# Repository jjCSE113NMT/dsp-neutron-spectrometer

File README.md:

# dsp-neutron-spectrometer

A place to keep all our material related to our senior design project.

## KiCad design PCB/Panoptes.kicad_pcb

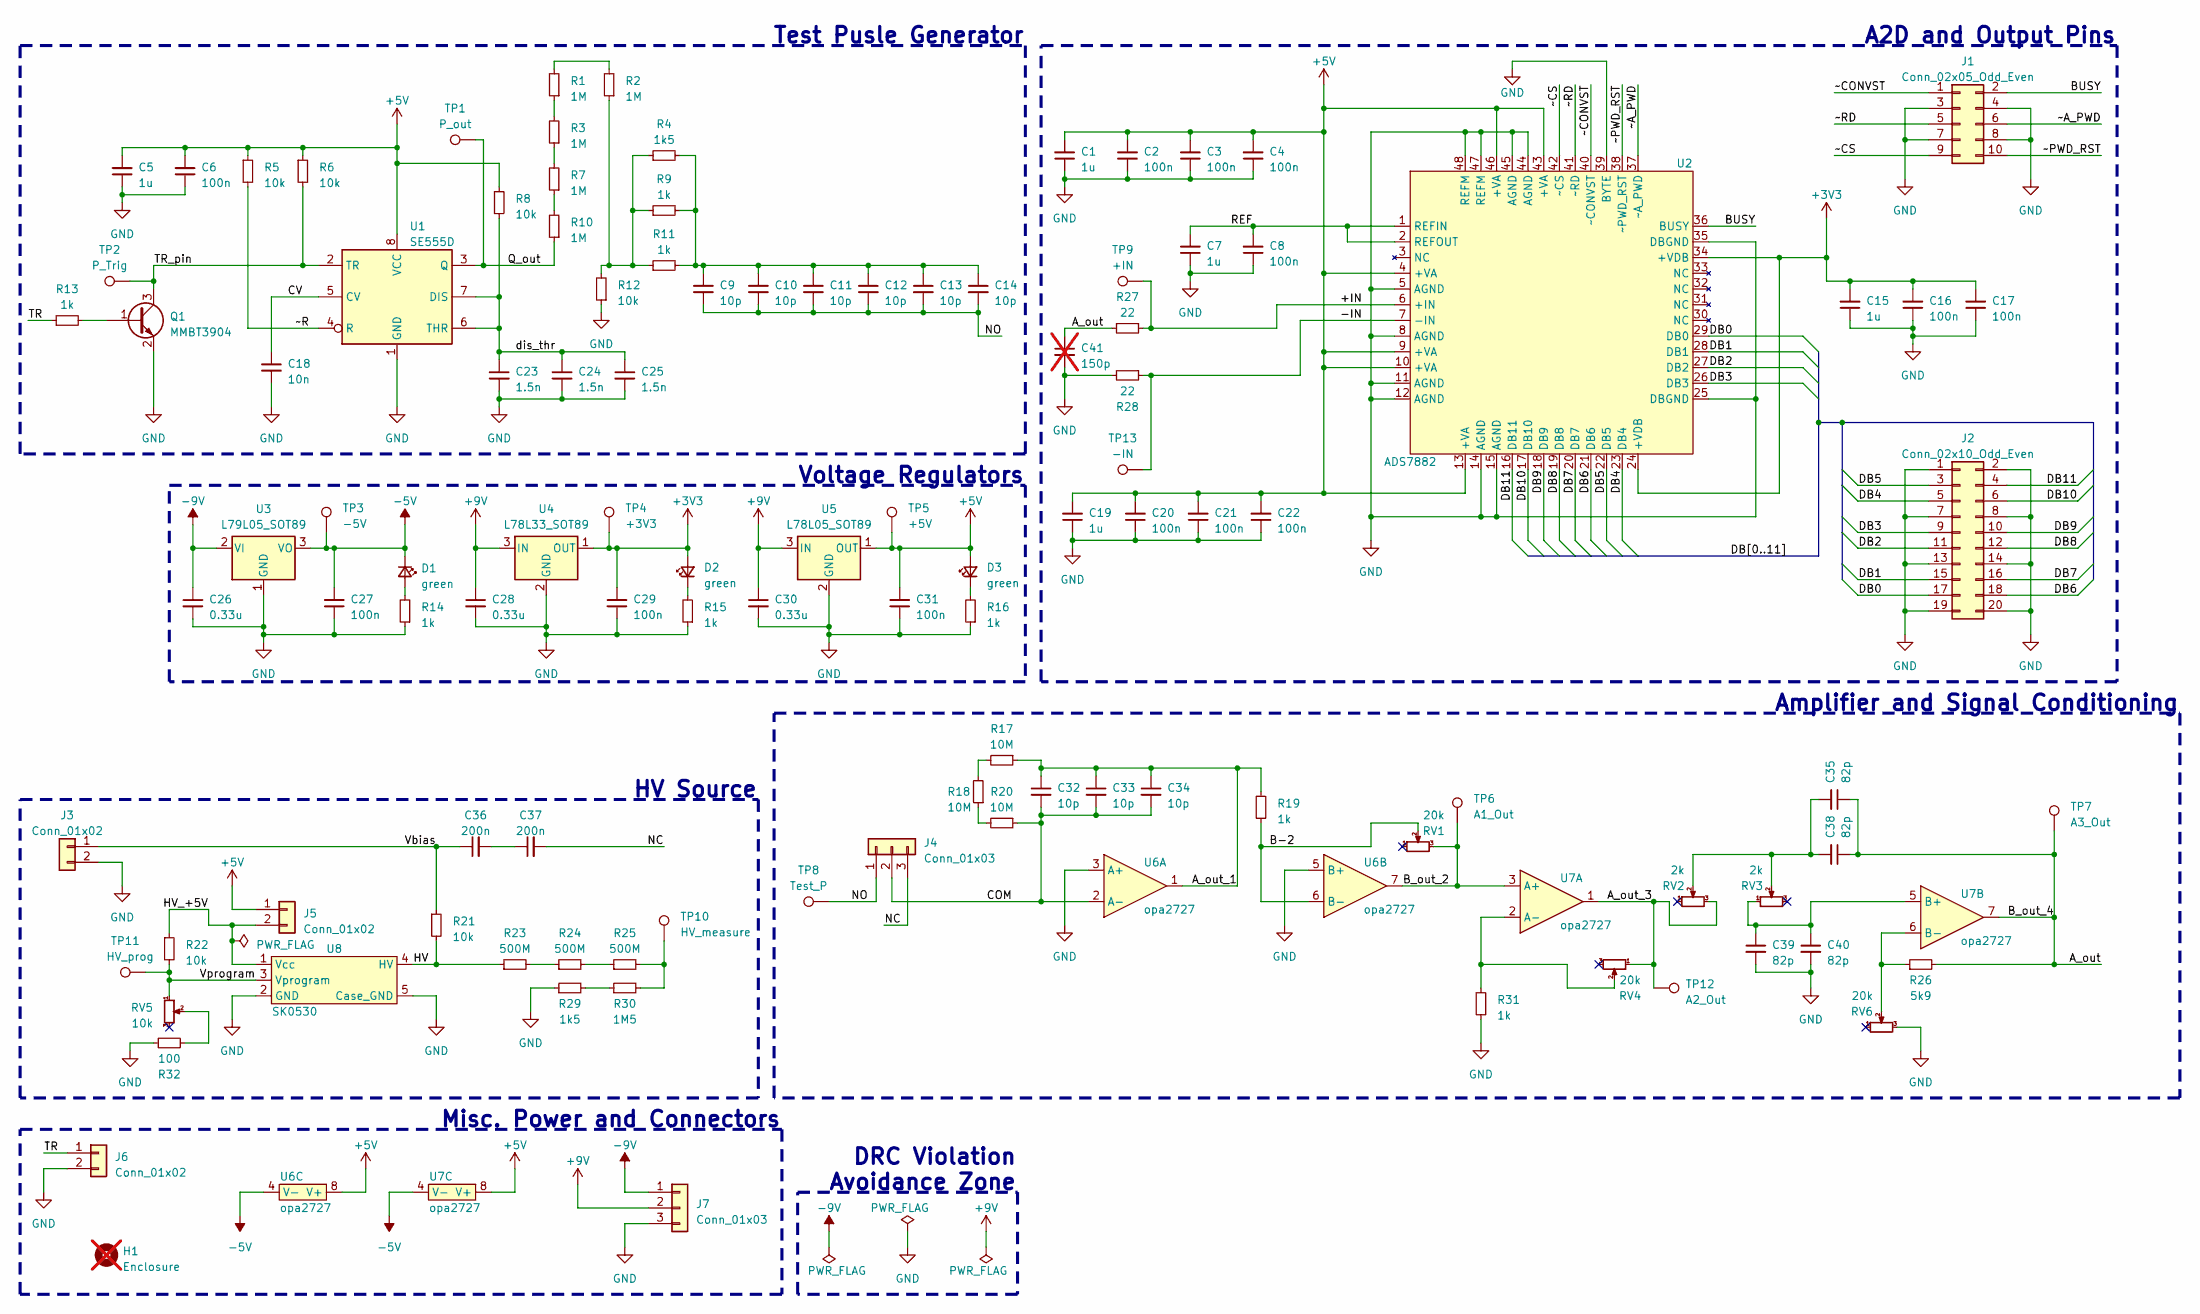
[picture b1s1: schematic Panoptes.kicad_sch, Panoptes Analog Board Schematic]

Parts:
C1, C5, C7, C15, C19: 1u; C_1206_3216Metric; MPN CL31B105KAHNNNE
C2, C3, C4, C6, C8, C16, C17, C20, C21, C22, C27, C29, C31: 100n; C_1206_3216Metric; MPN CL31B104KBCNNNC
C9, C10, C11, C12, C13, C14, C32, C33, C34: 10p; C_1206_3216Metric; MPN C1206C100F1HACAUTO
C18: 10n; C_1206_3216Metric; MPN C1206C103JARAC7800
C23, C24, C25: 1.5n; C_1206_3216Metric; MPN CC1206FRNPO9BN152
C26, C28, C30: 0.33u; C_1206_3216Metric; MPN CL31B334KBFNNNE
C35, C38, C39, C40: 82p; C_1206_3216Metric; MPN CC1206JRNPO9BN820
C36, C37: 200n; C_Disc_D10.5mm_W5.0mm_P7.50mm; MPN CK45-B3FD221KYGNA
C41: 150p; C_0603_1608Metric; not fitted
D1, D2, D3: green; LED_0805_2012Metric; MPN 150080VS75000
H1: Enclosure; n/a; MPN 1455N1201RD; not fitted
J1: Conn_02x05_Odd_Even; PinSocket_2x05_P2.54mm_Horizontal; MPN SFH11-PBPC-D05-RA-BK
J2: Conn_02x10_Odd_Even; PinSocket_2x10_P2.54mm_Horizontal; MPN SFH11-PBPC-D10-RA-BK
J3: Conn_01x02; tube pigtail; MPN n/a
J4: Conn_01x03; PinHeader_1x03_P2.54mm_Vertical; MPN n/a
J5: Conn_01x02; PinHeader_1x02_P2.54mm_Vertical; MPN n/a
J6: Conn_01x02; PinSocket_1x02_P2.54mm_Horizontal; MPN PPTC021LGBN-RC
J7: Conn_01x03; STX-3500-3NTR; MPN STX-3500-3NTR
Q1: MMBT3904; SOT-23-3; MPN MMBT3904-TP
R1, R2, R3, R7, R10: 1M; R_1206_3216Metric; MPN RMCF1206FT1M00
R4, R29: 1k5; R_1206_3216Metric; MPN RMCF1206FT1K50
R5, R6, R8, R12, R21, R22: 10k; R_1206_3216Metric; MPN RMCF1206FT10K0
R9, R11, R13, R14, R15, R16, R19, R31: 1k; R_1206_3216Metric; MPN RMCF1206FT1K00
R17, R18, R20: 10M; R_1206_3216Metric; MPN RMCF1206FT10M0
R23, R24, R25: 500M; R_Axial_DIN0207_L6.3mm_D2.5mm_P7.62mm_Horizontal; MPN HVA05FA500M
R26: 5k9; R_1206_3216Metric; MPN CRCW12065K90FKEA
R27, R28: 22; R_1206_3216Metric; MPN RMCF1206FT22R0
R30: 1M5; R_1206_3216Metric; MPN RC1206FR-071M5L
R32: 100; R_1206_3216Metric; MPN RMCF1206FG100R
RV1, RV4, RV6: 20k; Bourns 3361P; MPN 3361P-1-203GLF
RV2, RV3: 2k; Bourns 3361P; MPN 3361P-1-202GLF
RV5: 10k; Bourns 3361P; MPN 3361P-1-103GLF
TP1: P_out; PinHeader_1x01_P2.54mm_Vertical; MPN n/a
TP2: P_Trig; PinHeader_1x01_P2.54mm_Vertical; MPN n/a
TP3: -5V; PinHeader_1x01_P2.54mm_Vertical; MPN n/a
TP4: +3V3; PinHeader_1x01_P2.54mm_Vertical; MPN n/a
TP5: +5V; PinHeader_1x01_P2.54mm_Vertical; MPN n/a
TP6: A1_Out; PinHeader_1x01_P2.54mm_Vertical; MPN n/a
TP7: A3_Out; PinHeader_1x01_P2.54mm_Vertical; MPN n/a
TP8: Test_P; PinHeader_1x01_P2.54mm_Vertical; MPN n/a
TP9: +IN; PinHeader_1x01_P2.54mm_Vertical; MPN n/a
TP10: HV_measure; TestPoint_Pad_D1.0mm; MPN n/a
TP11: HV_prog; TestPoint_Pad_D1.0mm; MPN n/a
TP12: A2_Out; PinHeader_1x01_P2.54mm_Vertical; MPN n/a
TP13: -IN; PinHeader_1x01_P2.54mm_Vertical; MPN n/a
U1: SE555D; SOIC-8_3.9x4.9mm_P1.27mm; MPN SE555DR
U2: ADS7882; TQFP-48_7x7mm_P0.5mm; MPN ADS7882IPFBT
U3: L79L05_SOT89; SOT-89-3; MPN L79L05ACUTR
U4: L78L33_SOT89; SOT-89-3; MPN L78L33ACUTR
U5: L78L05_SOT89; SOT-89-3; MPN L78L05ACUTR
U6, U7: opa2727; DFN-8-1EP_3x3mm_P0.65mm_EP1.55x2.4mm; MPN OPA2727AIDRBT
U8: SK0530; MPN SK0530

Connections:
+3V3: C15.2, C16.2, C17.2, C29.2, D2.2 (A), TP4.1, U2.24 (+VDB), U2.34 (+VDB), U4.1 (OUT)
+5V: C1.2, C2.2, C3.2, C4.2, C5.2, C6.2, C19.2, C20.2, C21.2, C22.2, C31.2, D3.2 (A), J5.1, R5.1, R6.1, R8.1, TP5.1, U1.8 (VCC), U2.4 (+VA), U2.9 (+VA), U2.10 (+VA), U2.13 (+VA), U2.43 (+VA), U2.46 (+VA), U5.1 (OUT), U6.8 (V+), U7.8 (V+)
+9V: C28.1, C30.1, J7.2, U4.3 (IN), U5.3 (IN)
-5V: C27.2, D1.1 (K), TP3.1, U3.3 (VO), U6.4 (V-), U7.4 (V-)
-9V: C26.1, J7.1, U3.2 (VI)
/+IN: R27.1, TP9.1, U2.6 (+IN)
/-IN: R28.1, TP13.1, U2.7 (-IN)
/A_out: C35.1, C38.1, C41.1, R26.2, R27.2, TP7.1, U7.7
/A_out_1: C32.1, C33.1, C34.1, R17.1, R19.1, U6.1
/A_out_3: RV2.3, RV4.1, TP12.1, U7.1
/B-2: R19.2, RV1.2, U6.6 (B-)
/BUSY: J1.2, U2.36 (BUSY)
/B_out_2: RV1.3, TP6.1, U6.7, U7.3 (A+)
/COM: C32.2, C33.2, C34.2, J4.2, R20.1, U6.2 (A-)
/CV: C18.1, U1.5 (CV)
/DB0: J2.17, U2.29 (DB0)
/DB1: J2.15, U2.28 (DB1)
/DB2: J2.11, U2.27 (DB2)
/DB3: J2.9, U2.26 (DB3)
/DB4: J2.5, U2.23 (DB4)
/DB5: J2.3, U2.22 (DB5)
/DB6: J2.18, U2.21 (DB6)
/DB7: J2.16, U2.20 (DB7)
/DB8: J2.12, U2.19 (DB8)
/DB9: J2.10, U2.18 (DB9)
/DB10: J2.6, U2.17 (DB10)
/DB11: J2.4, U2.16 (DB11)
/HV: R21.2, R23.1, U8.4 (HV)
/HV_+5V: J5.2, R22.1, U8.1 (Vcc)
/NC: C37.2, J4.3
/NO: C9.2, C10.2, C11.2, C12.2, C13.2, C14.2, J4.1, TP8.1
/Q_out: R10.1, TP1.1, U1.3 (Q)
/REF: C7.2, C8.2, U2.1 (REFIN), U2.2 (REFOUT)
/TR: J6.1, R13.1
/TR_pin: Q1.3 (C), R6.2, TP2.1, U1.2 (TR)
/Vbias: C36.1, J3.1, R21.1
/Vprogram: R22.2, RV5.1, TP11.1, U8.3 (Vprogram)
/dis_thr: C23.1, C24.1, C25.1, R8.2, U1.6 (THR), U1.7 (DIS)
/~A_PWD: J1.6, U2.37 (~A_PWD)
/~CONVST: J1.1, U2.40 (~CONVST)
/~CS: J1.9, U2.42 (~CS)
/~PWD_RST: J1.10, U2.38 (~PWD_RST)
/~R: R5.2, U1.4 (R)
/~RD: J1.5, U2.41 (~RD)
GND: C1.1, C2.1, C3.1, C4.1, C5.1, C6.1, C7.1, C8.1, C15.1, C16.1, C17.1, C18.2, C19.1, C20.1, C21.1, C22.1, C23.2, C24.2, C25.2, C26.2, C27.1, C28.2, C29.1, C30.2, C31.1, C39.2, C40.2, C41.2, J1.3, J1.4, J1.7, J1.8, J2.1, J2.2, J2.7, J2.8, J2.13, J2.14, J2.19, J2.20, J3.2, J6.2, J7.3, Q1.2 (E), R12.1, R14.1, R15.1, R16.1, R28.2, R29.1, R31.1, R32.1, RV6.3, U1.1 (GND), U2.5 (AGND), U2.8 (AGND), U2.11 (AGND), U2.12 (AGND), U2.14 (AGND), U2.15 (AGND), U2.25 (DBGND), U2.35 (DBGND), U2.39 (BYTE), U2.44 (AGND), U2.45 (AGND), U2.47 (REFM), U2.48 (REFM), U3.1 (GND), U4.2 (GND), U5.2 (GND), U6.3 (A+), U6.5 (B+), U8.2 (GND), U8.5 (Case_GND)
unnamed: C9.1, C10.1, C11.1, C12.1, C13.1, C14.1, R4.2, R9.2, R11.2
unnamed: C35.2, C38.2, RV2.2, RV3.2
unnamed: C36.2, C37.1
unnamed: D1.2 (A), R14.2
unnamed: D2.1 (K), R15.2
unnamed: D3.1 (K), R16.2
unnamed: Q1.1 (B), R13.2
unnamed: R1.1, R3.2
unnamed: R1.2, R2.2
unnamed: R3.1, R7.2
unnamed: R7.1, R10.2
unnamed: R2.1, R4.1, R9.1, R11.1, R12.2
unnamed: R17.2, R18.2
unnamed: R18.1, R20.2
unnamed: R23.2, R24.1
unnamed: R24.2, R25.1
unnamed: R25.2, R30.2, TP10.1
unnamed: R29.2, R30.1
unnamed: R32.2, RV5.2
unnamed: R31.2, RV4.2, U7.2 (A-)
unnamed: C39.1, C40.1, RV3.1, U7.5 (B+)
unnamed: R26.1, RV6.2, U7.6 (B-)

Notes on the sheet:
Voltage Regulators
Test Pusle Generator
DRC Violation Avoidance Zone
Misc. Power and Connectors
Amplifier and Signal Conditioning
HV Source
A2D and Output Pins

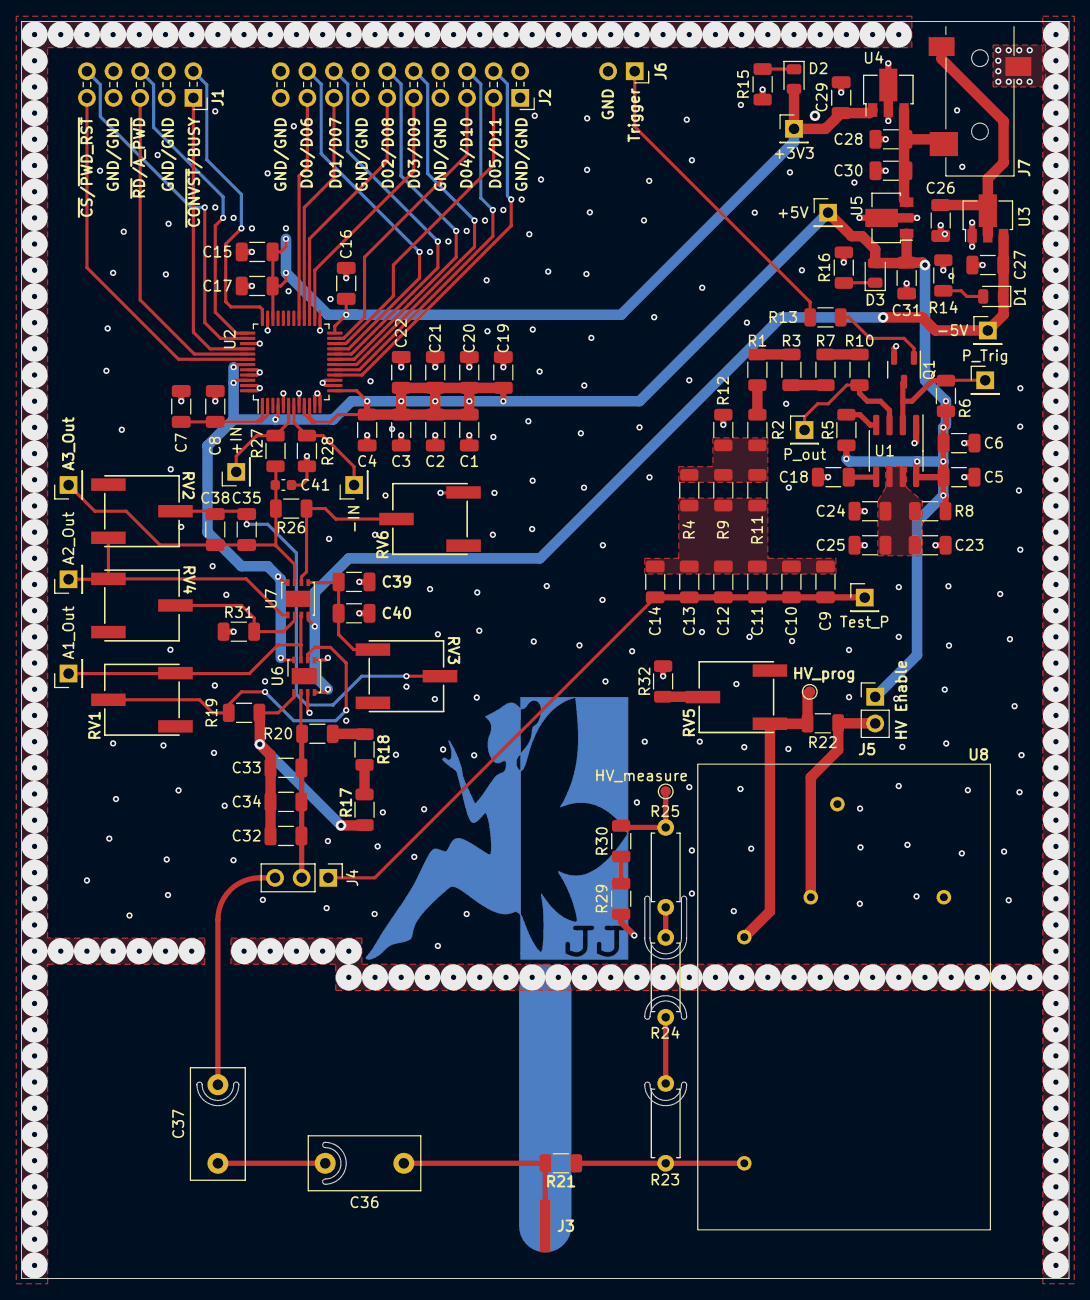
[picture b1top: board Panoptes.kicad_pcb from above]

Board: 4 copper layers, 100.0 x 120.0 mm, 111 parts (0 on the bottom side), 67 nets.

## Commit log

2022-10-05 Added some struture
2022-10-05 added some links and the tube 'datasheet'
2022-10-05 Added radiation textbook
2022-10-05 Added project proposal from Canvas
2022-10-07 added spice model for possible tail pulse generators
2023-03-15 Hopefully the last commit needed to fix this issue.
2023-04-08 start of rev.3
2023-04-10 All signals routed
2023-04-13 V3 completed
2023-04-17 Added DNP cap to ADC input.
2023-05-07 Added MCU code for stm32
